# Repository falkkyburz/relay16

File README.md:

# relay16
Relay board with 16 SPDT relays controlled by an Arduino Nano.

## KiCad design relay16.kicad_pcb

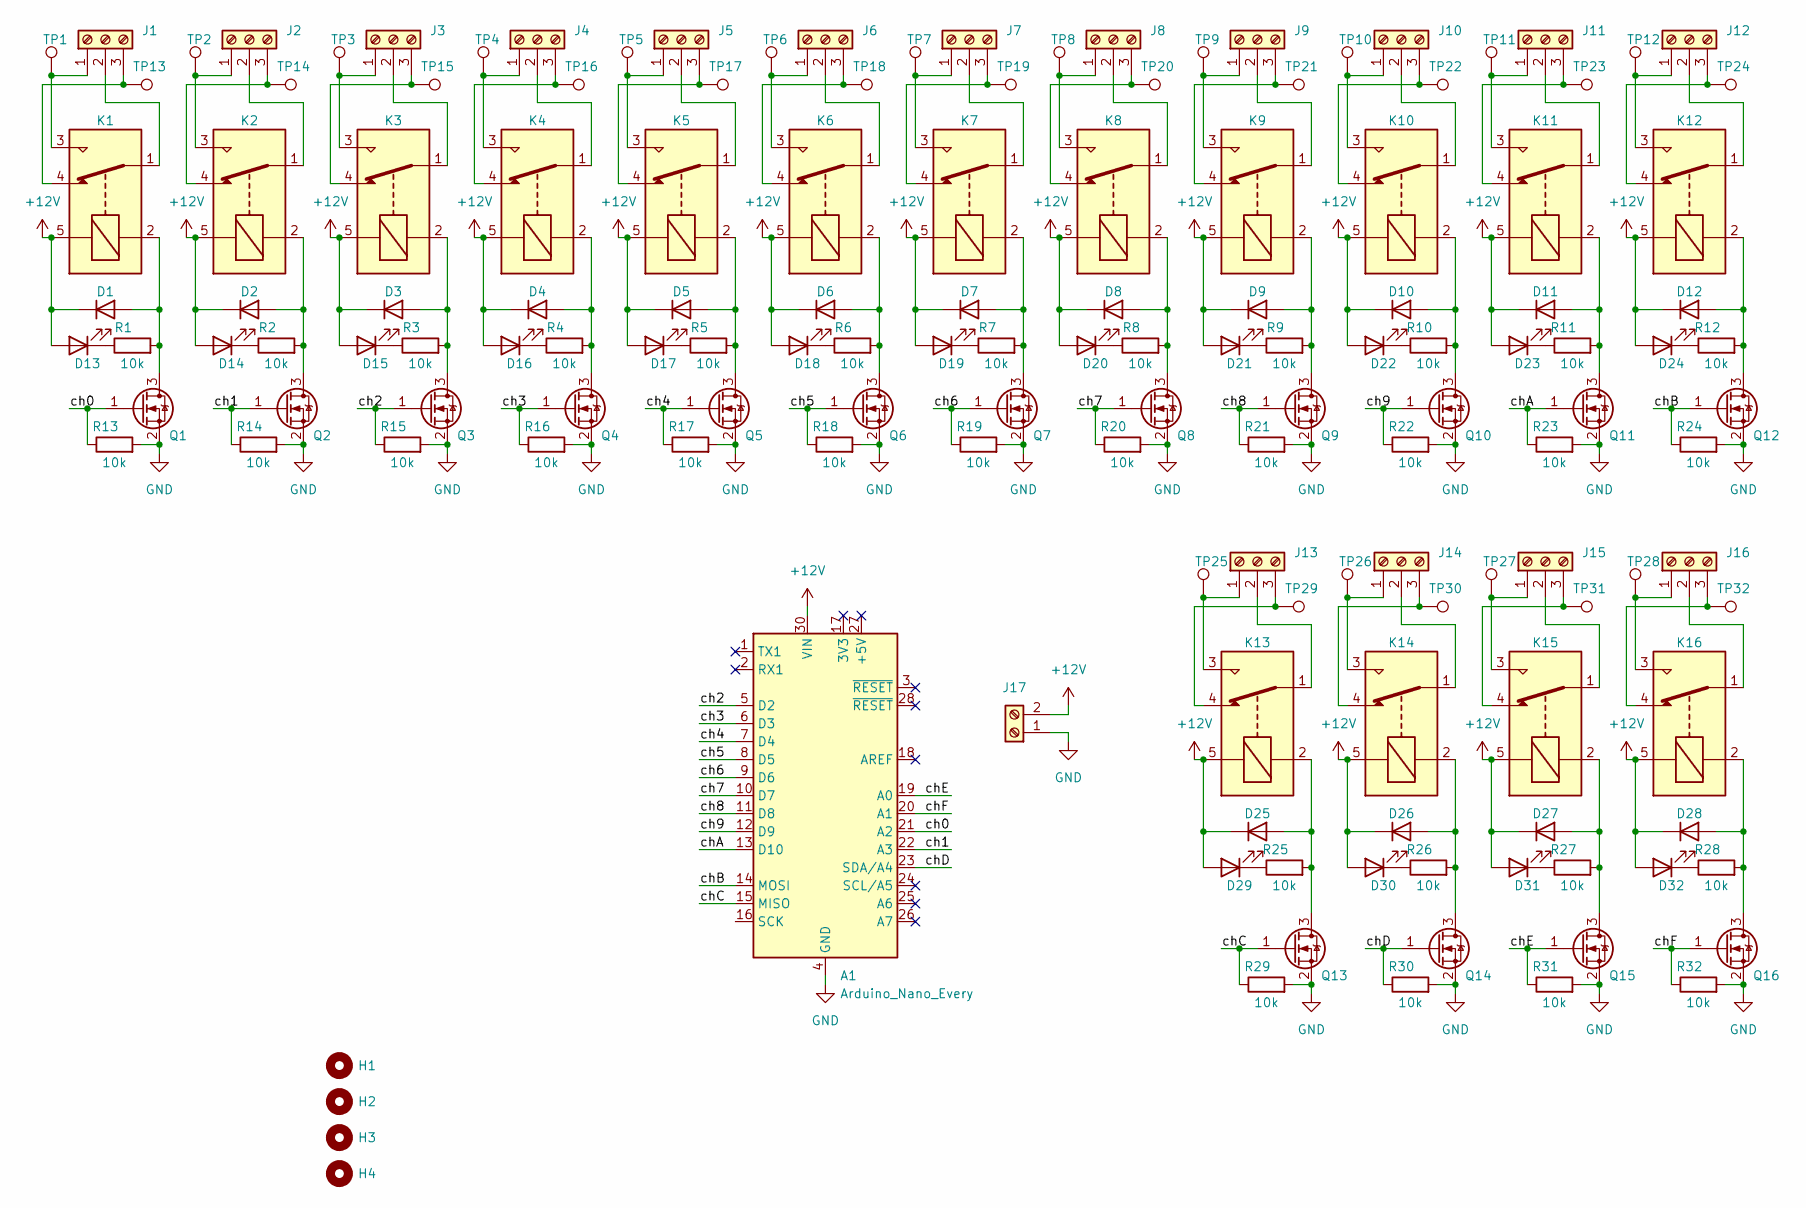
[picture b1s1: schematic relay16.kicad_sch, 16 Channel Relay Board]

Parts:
A1: Arduino_Nano_Every; Arduino_Nano
D1, D2, D3, D4, D5, D6, D7, D8, D9, D10, D11, D12, D25, D26, D27, D28: 1N4148W; D_SOD-123
D13, D14, D15, D16, D17, D18, D19, D20, D21, D22, D23, D24, D29, D30, D31, D32: LED; LED_0603_1608Metric
H1, H2, H3, H4: MountingHole; MountingHole_3.2mm_M3_Pad_Via
J1, J2, J3, J4, J5, J6, J7, J8, J9, J10, J11, J12, J13, J14, J15, J16: Screw_Terminal_01x03; TerminalBlock_Phoenix_MKDS-1,5-3_1x03_P5.00mm_Horizontal
J17: Screw_Terminal_01x02; TerminalBlock_Phoenix_MKDS-1,5-2_1x02_P5.00mm_Horizontal
K1, K2, K3, K4, K5, K6, K7, K8, K9, K10, K11, K12, K13, K14, K15, K16: SANYOU_SRD_Form_C; Relay_SPDT_SANYOU_SRD_Series_Form_C
Q1, Q2, Q3, Q4, Q5, Q6, Q7, Q8, Q9, Q10, Q11, Q12, Q13, Q14, Q15, Q16: 2N7002E; SOT-23
R1, R2, R3, R4, R5, R6, R7, R8, R9, R10, R11, R12, R13, R14, R15, R16, R17, R18, R19, R20, R21, R22, R23, R24, R25, R26, R27, R28, R29, R30, R31, R32: 10k; R_0603_1608Metric
TP1, TP2, TP3, TP4, TP5, TP6, TP7, TP8, TP9, TP10, TP11, TP12, TP13, TP14, TP15, TP16, TP17, TP18, TP19, TP20, TP21, TP22, TP23, TP24, TP25, TP26, TP27, TP28, TP29, TP30, TP31, TP32: TestPoint; TestPoint_Pad_2.5x2.5mm

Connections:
+12V: A1.30 (VIN), D1.1 (K), D2.1 (K), D3.1 (K), D4.1 (K), D5.1 (K), D6.1 (K), D7.1 (K), D8.1 (K), D9.1 (K), D10.1 (K), D11.1 (K), D12.1 (K), D13.2 (A), D14.2 (A), D15.2 (A), D16.2 (A), D17.2 (A), D18.2 (A), D19.2 (A), D20.2 (A), D21.2 (A), D22.2 (A), D23.2 (A), D24.2 (A), D25.1 (K), D26.1 (K), D27.1 (K), D28.1 (K), D29.2 (A), D30.2 (A), D31.2 (A), D32.2 (A), J17.2, K1.5, K2.5, K3.5, K4.5, K5.5, K6.5, K7.5, K8.5, K9.5, K10.5, K11.5, K12.5, K13.5, K14.5, K15.5, K16.5
/ch0: A1.21 (A2), Q1.1 (G), R13.1
/ch1: A1.22 (A3), Q2.1 (G), R14.1
/ch2: A1.5 (D2), Q3.1 (G), R15.1
/ch3: A1.6 (D3), Q4.1 (G), R16.1
/ch4: A1.7 (D4), Q5.1 (G), R17.1
/ch5: A1.8 (D5), Q6.1 (G), R18.1
/ch6: A1.9 (D6), Q7.1 (G), R19.1
/ch7: A1.10 (D7), Q8.1 (G), R20.1
/ch8: A1.11 (D8), Q9.1 (G), R21.1
/ch9: A1.12 (D9), Q10.1 (G), R22.1
/chA: A1.13 (D10), Q11.1 (G), R23.1
/chB: A1.14 (MOSI), Q12.1 (G), R24.1
/chC: A1.15 (MISO), Q13.1 (G), R29.1
/chD: A1.23 (SDA/A4), Q14.1 (G), R30.1
/chE: A1.19 (A0), Q15.1 (G), R31.1
/chF: A1.20 (A1), Q16.1 (G), R32.1
GND: A1.4 (GND), A1.29 (GND), J17.1, Q1.2 (S), Q2.2 (S), Q3.2 (S), Q4.2 (S), Q5.2 (S), Q6.2 (S), Q7.2 (S), Q8.2 (S), Q9.2 (S), Q10.2 (S), Q11.2 (S), Q12.2 (S), Q13.2 (S), Q14.2 (S), Q15.2 (S), Q16.2 (S), R13.2, R14.2, R15.2, R16.2, R17.2, R18.2, R19.2, R20.2, R21.2, R22.2, R23.2, R24.2, R29.2, R30.2, R31.2, R32.2
unnamed: D1.2 (A), K1.2, Q1.3 (D), R1.2
unnamed: D2.2 (A), K2.2, Q2.3 (D), R2.2
unnamed: D3.2 (A), K3.2, Q3.3 (D), R3.2
unnamed: D4.2 (A), K4.2, Q4.3 (D), R4.2
unnamed: D5.2 (A), K5.2, Q5.3 (D), R5.2
unnamed: D6.2 (A), K6.2, Q6.3 (D), R6.2
unnamed: D7.2 (A), K7.2, Q7.3 (D), R7.2
unnamed: D8.2 (A), K8.2, Q8.3 (D), R8.2
unnamed: D9.2 (A), K9.2, Q9.3 (D), R9.2
unnamed: D10.2 (A), K10.2, Q10.3 (D), R10.2
unnamed: D11.2 (A), K11.2, Q11.3 (D), R11.2
unnamed: D12.2 (A), K12.2, Q12.3 (D), R12.2
unnamed: D13.1 (K), R1.1
unnamed: D14.1 (K), R2.1
unnamed: D15.1 (K), R3.1
unnamed: D16.1 (K), R4.1
unnamed: D17.1 (K), R5.1
unnamed: D18.1 (K), R6.1
unnamed: D19.1 (K), R7.1
unnamed: D20.1 (K), R8.1
unnamed: D21.1 (K), R9.1
unnamed: D22.1 (K), R10.1
unnamed: D23.1 (K), R11.1
unnamed: D24.1 (K), R12.1
unnamed: D25.2 (A), K13.2, Q13.3 (D), R25.2
unnamed: D26.2 (A), K14.2, Q14.3 (D), R26.2
unnamed: D27.2 (A), K15.2, Q15.3 (D), R27.2
unnamed: D28.2 (A), K16.2, Q16.3 (D), R28.2
unnamed: D29.1 (K), R25.1
unnamed: D30.1 (K), R26.1
unnamed: D31.1 (K), R27.1
unnamed: D32.1 (K), R28.1
unnamed: J1.1, K1.3, TP1.1
unnamed: J1.2, K1.1
unnamed: J1.3, K1.4, TP13.1
unnamed: J2.1, K2.3, TP2.1
unnamed: J2.2, K2.1
unnamed: J2.3, K2.4, TP14.1
unnamed: J3.1, K3.3, TP3.1
unnamed: J3.2, K3.1
unnamed: J3.3, K3.4, TP15.1
unnamed: J4.1, K4.3, TP4.1
unnamed: J4.2, K4.1
unnamed: J4.3, K4.4, TP16.1
unnamed: J5.1, K5.3, TP5.1
unnamed: J5.2, K5.1
unnamed: J5.3, K5.4, TP17.1
unnamed: J6.1, K6.3, TP6.1
unnamed: J6.2, K6.1
unnamed: J6.3, K6.4, TP18.1
unnamed: J7.1, K7.3, TP7.1
unnamed: J7.2, K7.1
unnamed: J7.3, K7.4, TP19.1
unnamed: J8.1, K8.3, TP8.1
unnamed: J8.2, K8.1
unnamed: J8.3, K8.4, TP20.1
unnamed: J9.1, K9.3, TP9.1
unnamed: J9.2, K9.1
unnamed: J9.3, K9.4, TP21.1
unnamed: J10.1, K10.3, TP10.1
unnamed: J10.2, K10.1
unnamed: J10.3, K10.4, TP22.1
unnamed: J11.1, K11.3, TP11.1
unnamed: J11.2, K11.1
unnamed: J11.3, K11.4, TP23.1
unnamed: J12.1, K12.3, TP12.1
unnamed: J12.2, K12.1
unnamed: J12.3, K12.4, TP24.1
unnamed: J13.1, K13.3, TP25.1
unnamed: J13.2, K13.1
unnamed: J13.3, K13.4, TP29.1
unnamed: J14.1, K14.3, TP26.1
unnamed: J14.2, K14.1
unnamed: J14.3, K14.4, TP30.1
unnamed: J15.1, K15.3, TP27.1
unnamed: J15.2, K15.1
unnamed: J15.3, K15.4, TP31.1
unnamed: J16.1, K16.3, TP28.1
unnamed: J16.2, K16.1
unnamed: J16.3, K16.4, TP32.1

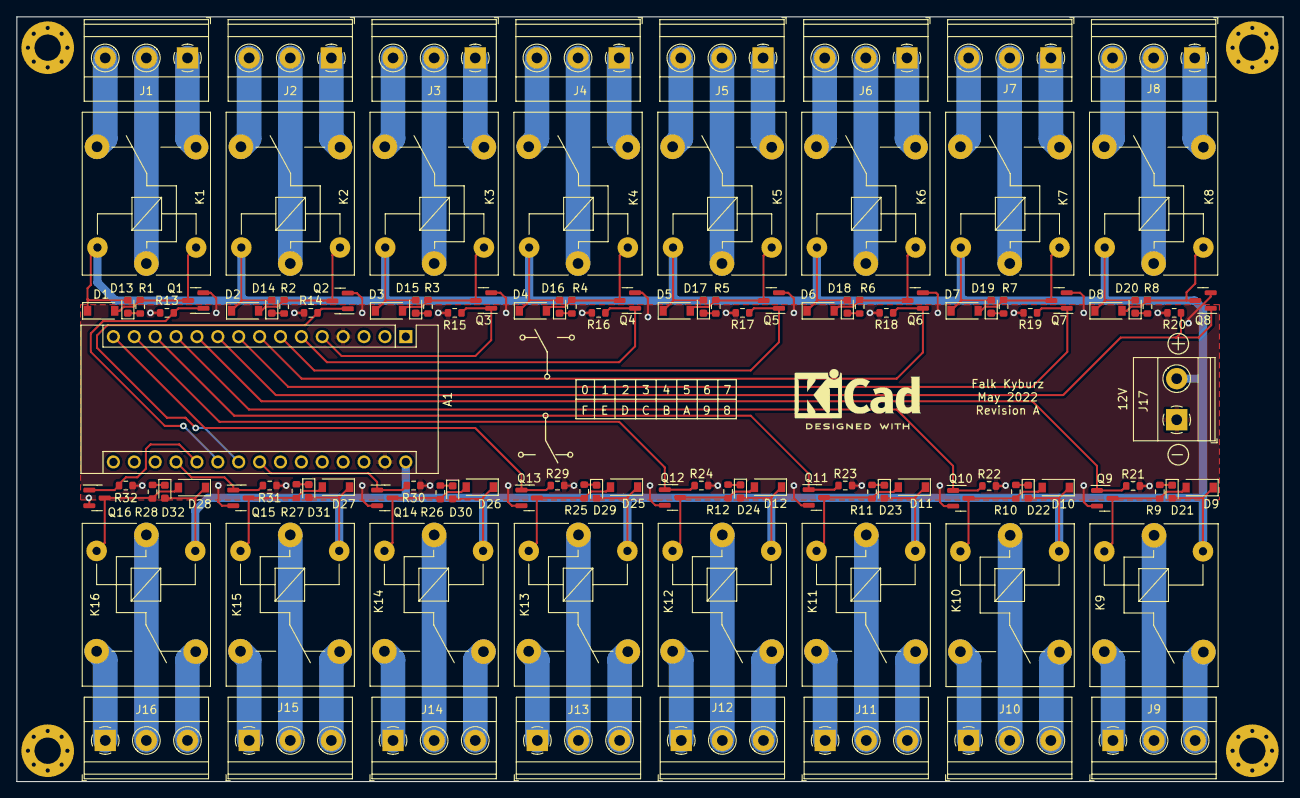
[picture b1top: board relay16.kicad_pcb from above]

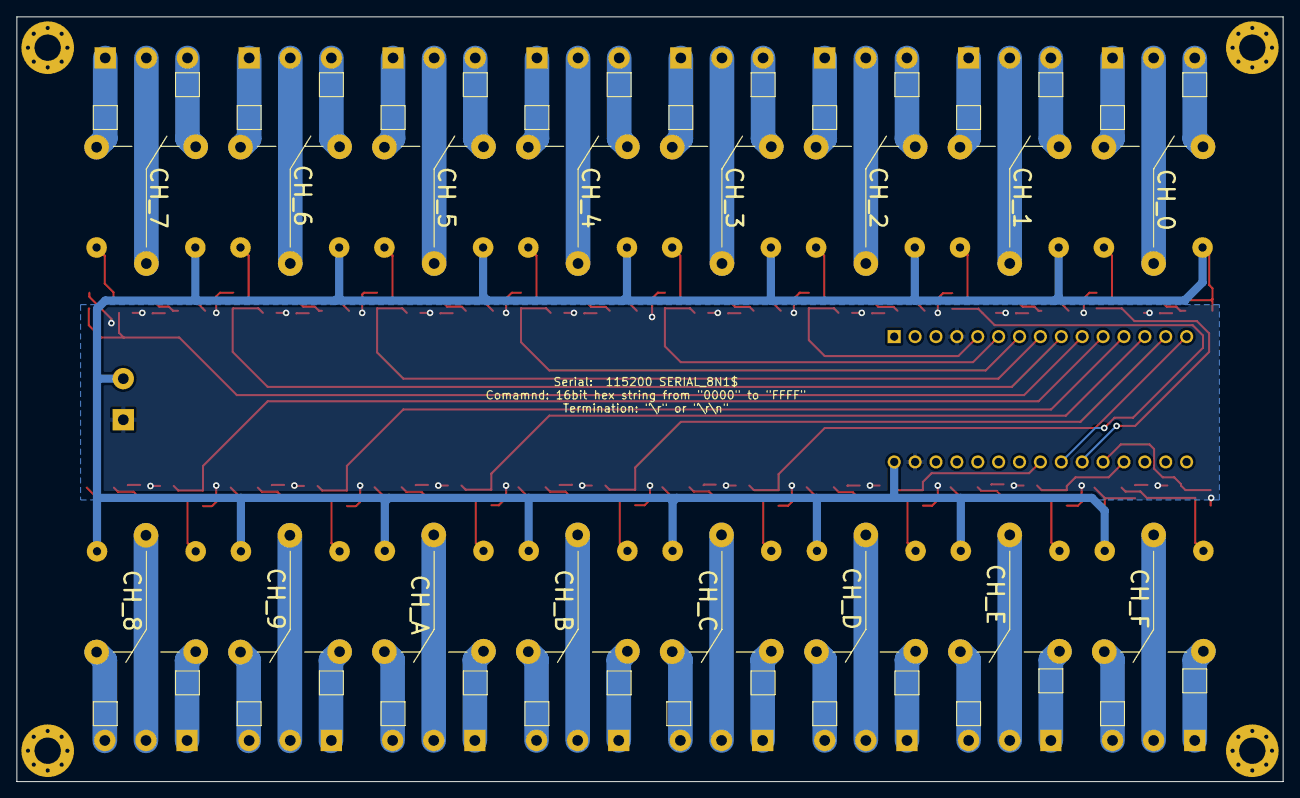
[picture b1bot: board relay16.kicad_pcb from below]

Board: 2 copper layers, 154.0 x 93.0 mm, 150 parts (32 on the bottom side), 98 nets.

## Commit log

2022-05-15 Initial commit of files.
2022-05-22 Data as ordered.
2022-06-01 Added Arduino sketch relay16.ino Changed LED resistor value from 10k to 2.2k. Successfully commissioned first prototype.
2022-06-01 Added integer command configuration in relay16.ino
2022-06-02 Added live configuration to relay16.ino
